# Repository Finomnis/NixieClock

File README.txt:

Repository structure follows
https://medium.com/inventhub/better-manage-kicad-projects-using-git-8d06e1310af8

Hardware — contains the KiCAD Project, Schematics & Layout and Project Libraries
Firmware — contains any software developed for the Hardware
Docs — contains any data sheets or documentations
Production — contains the gerber files, BOM or anything required by the fabrication houses
Simulation — contains any simulation files and generated results
CAD — contains the 3D models and mechanical designs for enclosures or support

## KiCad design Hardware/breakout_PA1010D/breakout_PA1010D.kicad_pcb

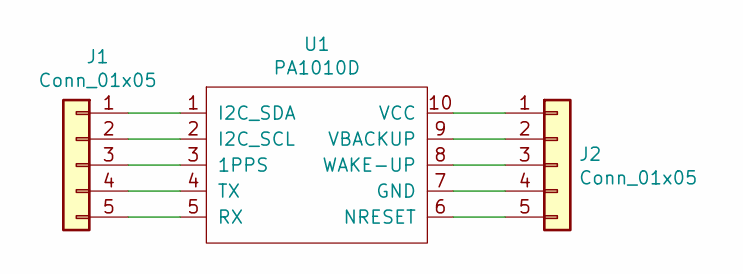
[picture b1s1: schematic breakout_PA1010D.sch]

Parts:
J1, J2: Conn_01x05; PinHeader_1x05_P2.54mm_Vertical
U1: PA1010D

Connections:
unnamed: J1.1, U1.1 (I2C_SDA)
unnamed: J1.2, U1.2 (I2C_SCL)
unnamed: J1.3, U1.3 (1PPS)
unnamed: J1.4, U1.4 (TX)
unnamed: J1.5, U1.5 (RX)
unnamed: J2.1, U1.10 (VCC)
unnamed: J2.2, U1.9 (VBACKUP)
unnamed: J2.3, U1.8 (WAKE-UP)
unnamed: J2.4, U1.7 (GND)
unnamed: J2.5, U1.6 (NRESET)

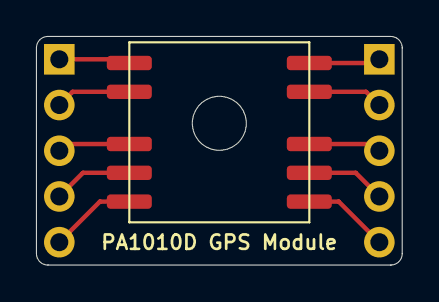
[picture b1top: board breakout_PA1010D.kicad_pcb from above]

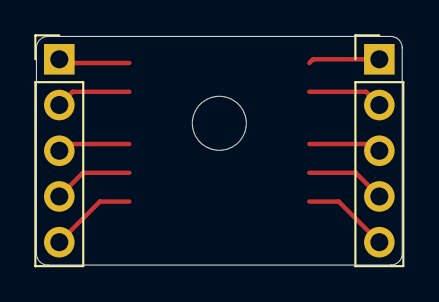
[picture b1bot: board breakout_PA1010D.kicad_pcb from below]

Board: 2 copper layers, 20.3 x 12.7 mm, 3 parts (2 on the bottom side), 10 nets.

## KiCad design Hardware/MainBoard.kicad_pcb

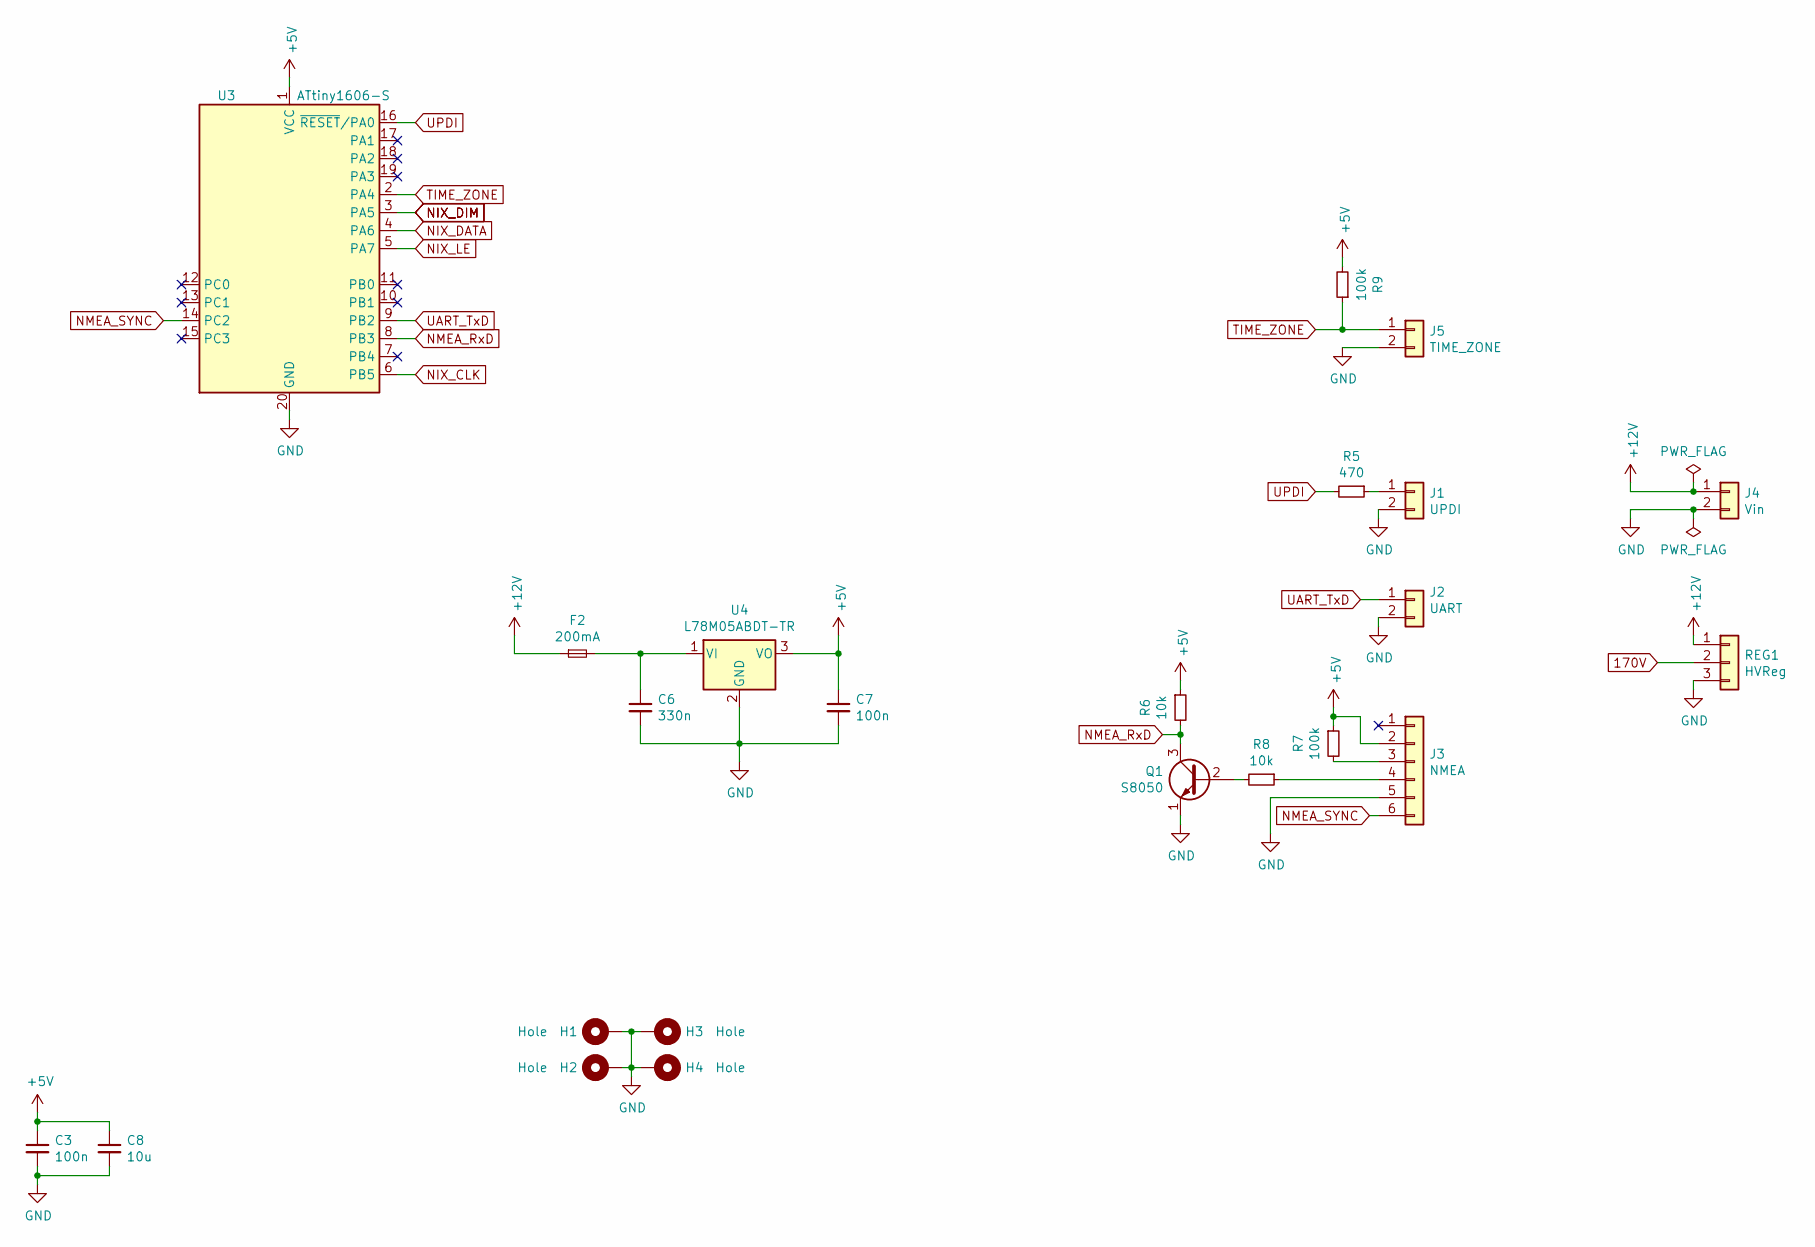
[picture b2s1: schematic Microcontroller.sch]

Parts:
C3, C7: 100n; C_0603_1608Metric
C6: 330n; C_0603_1608Metric
C8: 10u; C_0805_2012Metric
F2: 200mA; Fuse_0603_1608Metric
H1, H2, H3, H4: Hole; MountingHole_2.7mm_M2.5_Pad_Via
J1: UPDI; PinHeader_1x02_P2.54mm_Vertical
J2: UART; PinHeader_1x02_P2.54mm_Vertical
J3: NMEA; PinHeader_1x06_P1.27mm_Vertical
J4: Vin; PinHeader_1x02_P2.54mm_Vertical
J5: TIME_ZONE; PinHeader_1x02_P2.54mm_Vertical
Q1: S8050; SOT-23
R5: 470; R_0603_1608Metric
R6, R8: 10k; R_0603_1608Metric
R7, R9: 100k; R_0603_1608Metric
REG1: HVReg; NCH8200HV
U3: ATtiny1606-S; SOIC-20W_7.5x12.8mm_P1.27mm
U4: L78M05ABDT-TR; TO-252-2

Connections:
170V: REG1.2; also elsewhere on the board
+5V: C3.1, C7.1, C8.1, J3.2, R6.1, R7.1, R9.2, U3.1 (VCC), U4.3 (VO); also elsewhere on the board
+12V: F2.1, J4.1, REG1.1
GND: C3.2, C6.2, C7.2, C8.2, H1.1, H2.1, H3.1, H4.1, J1.2, J2.2, J3.5, J4.2, J5.2, Q1.1 (E), REG1.3, U3.20 (GND), U4.2 (GND); also elsewhere on the board
NIX_CLK: U3.6 (PB5); also elsewhere on the board
NIX_DATA: U3.4 (PA6); also elsewhere on the board
NIX_DIM: U3.3 (PA5); also elsewhere on the board
NIX_LE: U3.5 (PA7); also elsewhere on the board
NMEA_RxD: Q1.3 (C), R6.2, U3.8 (PB3)
NMEA_SYNC: J3.6, U3.14 (PC2)
unnamed: C6.1, F2.2, U4.1 (VI)
unnamed: J1.1, R5.1
unnamed: J3.3, R7.2
unnamed: J3.4, R8.1
unnamed: Q1.2 (B), R8.2
TIME_ZONE: J5.1, R9.1, U3.2 (PA4)
UART_TxD: J2.1, U3.9 (PB2)
UPDI: R5.2, U3.16 (~RESET~/PA0)

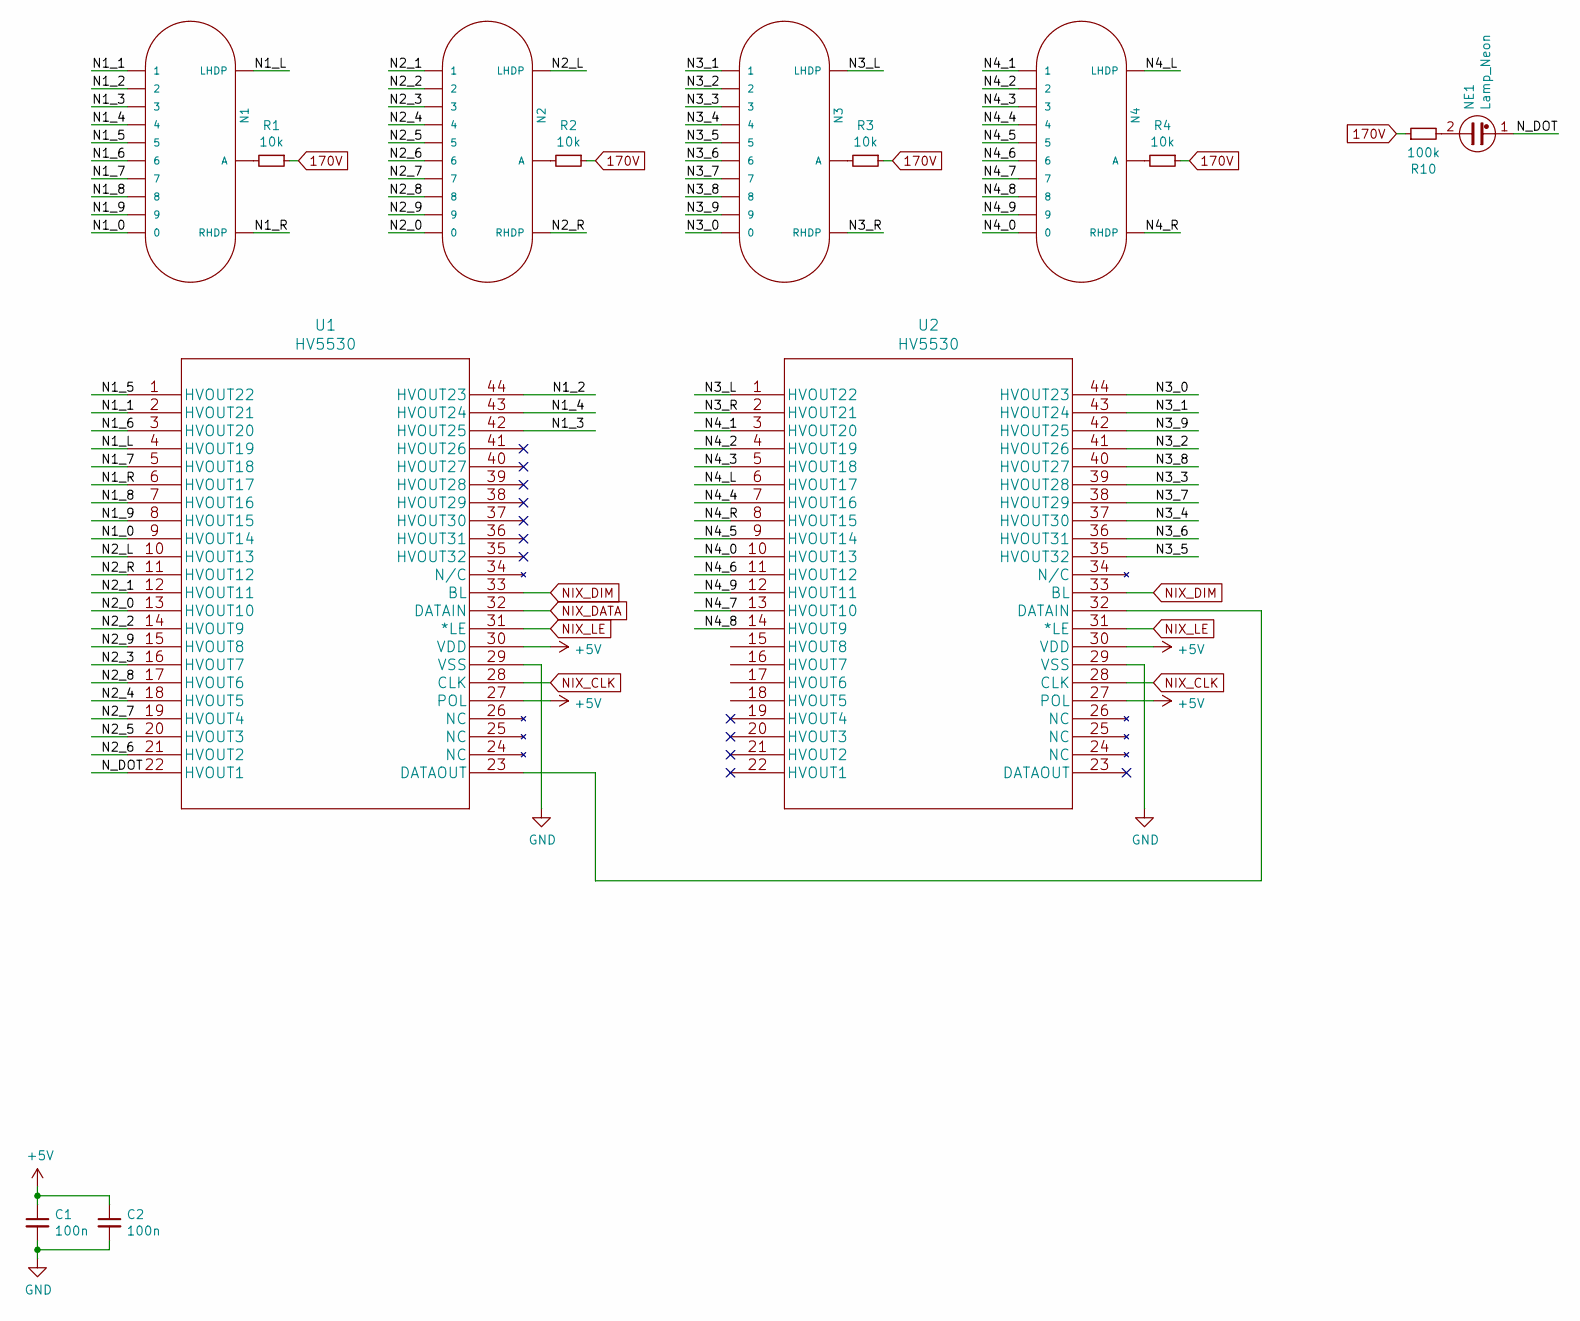
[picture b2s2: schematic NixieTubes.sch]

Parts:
C1, C2: 100n; C_0603_1608Metric
N1, N2, N3, N4: IN-14
NE1: Lamp_Neon; Colon
R1, R2, R3, R4: 10k; R_1206_3216Metric
R10: 100k; R_1206_3216Metric
U1, U2: HV5530; PQFP-44_10x10mm_P0.8mm

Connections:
170V: R1.1, R2.1, R3.1, R4.1, R10.1; also elsewhere on the board
+5V: C1.1, C2.1, U1.27 (POL), U1.30 (VDD), U2.27 (POL), U2.30 (VDD); also elsewhere on the board
/NixieTubes/N1_0: N1.0, U1.9 (HVOUT14)
/NixieTubes/N1_1: N1.1, U1.2 (HVOUT21)
/NixieTubes/N1_2: N1.2, U1.44 (HVOUT23)
/NixieTubes/N1_3: N1.3, U1.42 (HVOUT25)
/NixieTubes/N1_4: N1.4, U1.43 (HVOUT24)
/NixieTubes/N1_5: N1.5, U1.1 (HVOUT22)
/NixieTubes/N1_6: N1.6, U1.3 (HVOUT20)
/NixieTubes/N1_7: N1.7, U1.5 (HVOUT18)
/NixieTubes/N1_8: N1.8, U1.7 (HVOUT16)
/NixieTubes/N1_9: N1.9, U1.8 (HVOUT15)
/NixieTubes/N1_L: N1.LHDP, U1.4 (HVOUT19)
/NixieTubes/N1_R: N1.RHDP, U1.6 (HVOUT17)
/NixieTubes/N2_0: N2.0, U1.13 (HVOUT10)
/NixieTubes/N2_1: N2.1, U1.12 (HVOUT11)
/NixieTubes/N2_2: N2.2, U1.14 (HVOUT9)
/NixieTubes/N2_3: N2.3, U1.16 (HVOUT7)
/NixieTubes/N2_4: N2.4, U1.18 (HVOUT5)
/NixieTubes/N2_5: N2.5, U1.20 (HVOUT3)
/NixieTubes/N2_6: N2.6, U1.21 (HVOUT2)
/NixieTubes/N2_7: N2.7, U1.19 (HVOUT4)
/NixieTubes/N2_8: N2.8, U1.17 (HVOUT6)
/NixieTubes/N2_9: N2.9, U1.15 (HVOUT8)
/NixieTubes/N2_L: N2.LHDP, U1.10 (HVOUT13)
/NixieTubes/N2_R: N2.RHDP, U1.11 (HVOUT12)
/NixieTubes/N3_0: N3.0, U2.44 (HVOUT23)
/NixieTubes/N3_1: N3.1, U2.43 (HVOUT24)
/NixieTubes/N3_2: N3.2, U2.41 (HVOUT26)
/NixieTubes/N3_3: N3.3, U2.39 (HVOUT28)
/NixieTubes/N3_4: N3.4, U2.37 (HVOUT30)
/NixieTubes/N3_5: N3.5, U2.35 (HVOUT32)
/NixieTubes/N3_6: N3.6, U2.36 (HVOUT31)
/NixieTubes/N3_7: N3.7, U2.38 (HVOUT29)
/NixieTubes/N3_8: N3.8, U2.40 (HVOUT27)
/NixieTubes/N3_9: N3.9, U2.42 (HVOUT25)
/NixieTubes/N3_L: N3.LHDP, U2.1 (HVOUT22)
/NixieTubes/N3_R: N3.RHDP, U2.2 (HVOUT21)
/NixieTubes/N4_0: N4.0, U2.10 (HVOUT13)
/NixieTubes/N4_1: N4.1, U2.3 (HVOUT20)
/NixieTubes/N4_2: N4.2, U2.4 (HVOUT19)
/NixieTubes/N4_3: N4.3, U2.5 (HVOUT18)
/NixieTubes/N4_4: N4.4, U2.7 (HVOUT16)
/NixieTubes/N4_5: N4.5, U2.9 (HVOUT14)
/NixieTubes/N4_6: N4.6, U2.11 (HVOUT12)
/NixieTubes/N4_7: N4.7, U2.13 (HVOUT10)
/NixieTubes/N4_8: N4.8, U2.14 (HVOUT9)
/NixieTubes/N4_9: N4.9, U2.12 (HVOUT11)
/NixieTubes/N4_L: N4.LHDP, U2.6 (HVOUT17)
/NixieTubes/N4_R: N4.RHDP, U2.8 (HVOUT15)
/NixieTubes/N_DOT: NE1.1, U1.22 (HVOUT1)
GND: C1.2, C2.2, U1.29 (VSS), U2.29 (VSS); also elsewhere on the board
NIX_CLK: U1.28 (CLK), U2.28 (CLK); also elsewhere on the board
NIX_DATA: U1.32 (DATAIN); also elsewhere on the board
NIX_DIM: U1.33 (BL), U2.33 (BL); also elsewhere on the board
NIX_LE: U1.31 (*LE), U2.31 (*LE); also elsewhere on the board
unnamed: N1.A, R1.2
unnamed: N2.A, R2.2
unnamed: N3.A, R3.2
unnamed: N4.A, R4.2
unnamed: NE1.2, R10.2
unnamed: U1.23 (DATAOUT), U2.32 (DATAIN)

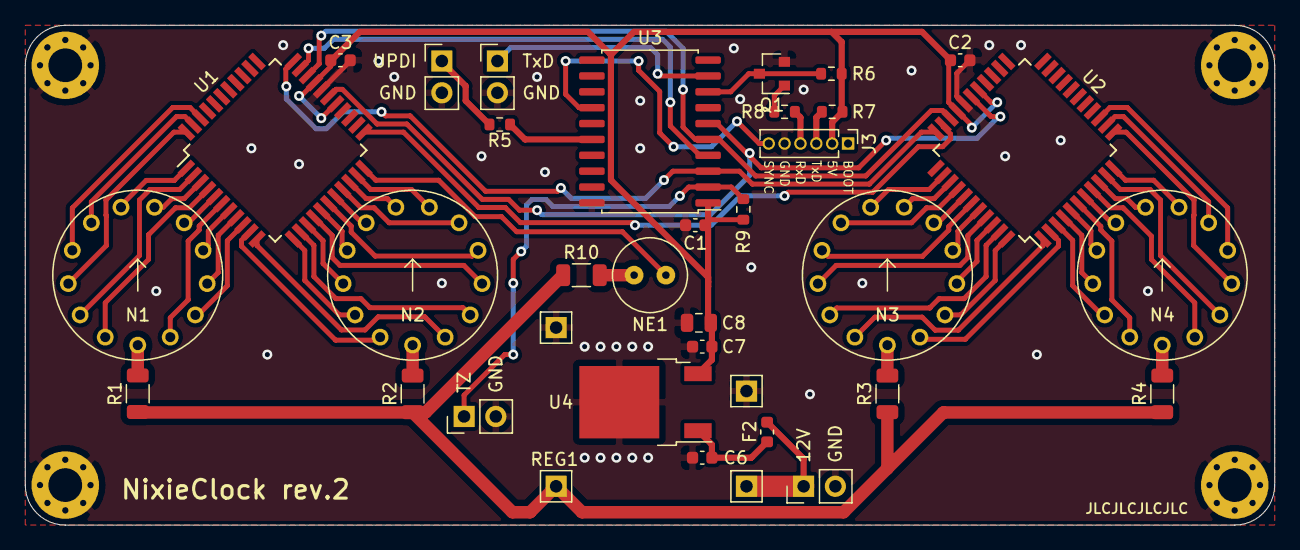
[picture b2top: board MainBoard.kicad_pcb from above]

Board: 2 copper layers, 100.0 x 40.0 mm, 37 parts (0 on the bottom side), 73 nets.

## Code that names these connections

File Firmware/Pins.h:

#pragma once

#include <Arduino.h>

struct PINS_t
{
    const uint8_t NIXIE_DIM = PIN_PA5;
    const uint8_t NIXIE_DATA = PIN_PA6;
    const uint8_t NIXIE_LATCH = PIN_PA7;
    const uint8_t NIXIE_CLK = PIN_PB5;

    const uint8_t TIME_ZONE = PIN_PA4;
    const uint8_t NMEA_SYNC = PIN_PC2;

    void initializePins() const
    {
        pinMode(NIXIE_DIM, OUTPUT);
        pinMode(NIXIE_DATA, OUTPUT);
        pinMode(NIXIE_LATCH, OUTPUT);
        pinMode(NIXIE_CLK, OUTPUT);
        pinMode(TIME_ZONE, INPUT);
        pinMode(NMEA_SYNC, INPUT);

        // Set PWM frequency
        constexpr int TCA = 0x0A00;
        *((char *)TCA) = 0b00001101;
    }
};

extern const PINS_t PINS;

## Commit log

2020-09-30 Second initial commit
2020-09-30 Add RealTimeTimestamp
2020-09-30 Finished RealTimeClock
2020-10-01 DCF Filtering
2020-10-01 Refined dcf filtering
2020-10-01 Cleanup: renamed dcf77interrupt
2020-10-01 Dcf parsing
2020-10-02 Added conversion to unix time to timestamp
2020-10-02 Reworked RealTimeClock to be interrupt compatible
2020-10-02 Added Dcf77 validation time stamps
2020-10-02 Create Dcf77::handleTimeData, added timestamp const correctness
2020-10-02 Added providing of data to DCF, added verbosity levels
2020-10-02 Add retrieval function to Dcf
2020-10-02 Use DCF to sync RTC
2020-10-02 Fixed blink duration during update was too short
2020-10-02 Add SineAnimation
2020-10-02 Remove unused animation tables
2020-10-02 Add NixieDisplay
2020-10-02 Remove unnecessary lock from RealTimeClock
2020-10-02 Add status info functions to Dcf77
2020-10-02 Add setDots to NixieDisplay
2020-10-02 Add missing pins, fixes too high energy consumption due to floating wires
2020-10-02 Implement most of the clock logic
2020-10-02 Add loading animation when clock sync gets too old
2020-10-02 Raised up-to-date timeout to 4 hours
2020-10-03 Add nixie shift register output
2020-10-04 Disable colon blinking, was too stressful
2020-10-04 Made console rendering configurable
2020-10-04 Minor fix in RealTimeClock::init
2020-10-04 Relaxed systemtime offset threshold, added colon blinking on resynchronization
2020-10-04 Fixed clock resetting on flash
2020-10-04 Fixed isInitialized breaking in year 2100
2020-10-04 Add DimAnimation
2020-10-04 Add setBrightness method to NixieDisplay
2020-10-04 Add intensity dimming between 23:00-07:00
2020-10-04 Moved setting to Settings.h
2020-10-05 Fix nixies getting dimmed during initial sync
2020-10-06 Disable resync indicator, as sync doesn't work reliable enough, and clock accuracy is already fine without resync
2020-11-03 Switched time source to NMEA GPS
2020-11-04 Clock now displays loading animation if NMEA got disconnected
2020-11-04 Added Readme
2020-11-04 First Hardware commit
2020-11-04 Add IN14 datasheet
2020-11-04 Fix library paths
2020-11-04 Add Libraries
2020-11-04 Add DCF and GPS docs
2020-11-04 Reworked Schematic for GPS
2020-11-06 Start rework
2020-11-06 Cleanup libraries
2020-11-06 Add signal inversion for NMEA
2020-11-06 Fix packages, route left nixies
2020-11-06 More layouting
2020-11-08 Replace LDO
2020-11-08 Route UPDI and UART
2020-11-08 Routed right nixies
2020-11-08 Finish routing connections
2020-11-08 Add ground vias
2020-11-08 Minor fixes to ground plane
2020-11-08 Change mounting holes to M2.5
2020-11-08 Add timezone switch
2020-11-08 Moved NMEA connector further to the back
2020-11-08 Silk screen fixes
2020-11-08 Fix another silkscreen
2020-11-08 Production: v2
2020-11-08 Add forgotten file. Still belongs to v2
2020-11-08 Fix missing wrapping at 24:00
2020-11-17 Fix shift register polarities
2020-11-22 Add Nixie Alignment Helper
2020-11-29 Fix Q1 pinout
2020-11-29 Add verification measurements to NixieAlignmentHelper
2020-12-28 Update pins for new board
2020-12-28 Fix firmware.ino
2020-12-28 Fix pin mappings in NixieDisplay.cpp
2020-12-28 Fix pins.h name, part1
2020-12-28 fix pins.h name, part2
2020-12-28 Remove RealTimeClock firmware code
2020-12-28 Add timezone switch to Nmea.cpp
2020-12-28 Minor refactoring in NixieDisplay.cpp
2021-02-04 Reduce pwm frequency to minimize feeping noise
2021-05-09 Add flash instructions, adjust PWM frequency
2021-08-14 Move dimming time to 22:00
2021-08-15 Change firmware framework to platformio
2021-11-13 Move Hardware to Hardware/v1
2021-11-13 Add PA1010D breakout board
2021-11-13 Fix minor text issue in PA1010D footprint
2021-11-13 Fix forgotten save
2021-11-26 Add firmware skeleton for v3
2021-11-27 Fix firmware crate name; add blinky example
2021-12-01 Add rtic example
2022-01-10 Initial body
2022-01-10 4way mirror
2022-01-14 Add solidworks case
2022-01-24 Extract Dimensions from Solidworks, as preparation for canceled subscription
